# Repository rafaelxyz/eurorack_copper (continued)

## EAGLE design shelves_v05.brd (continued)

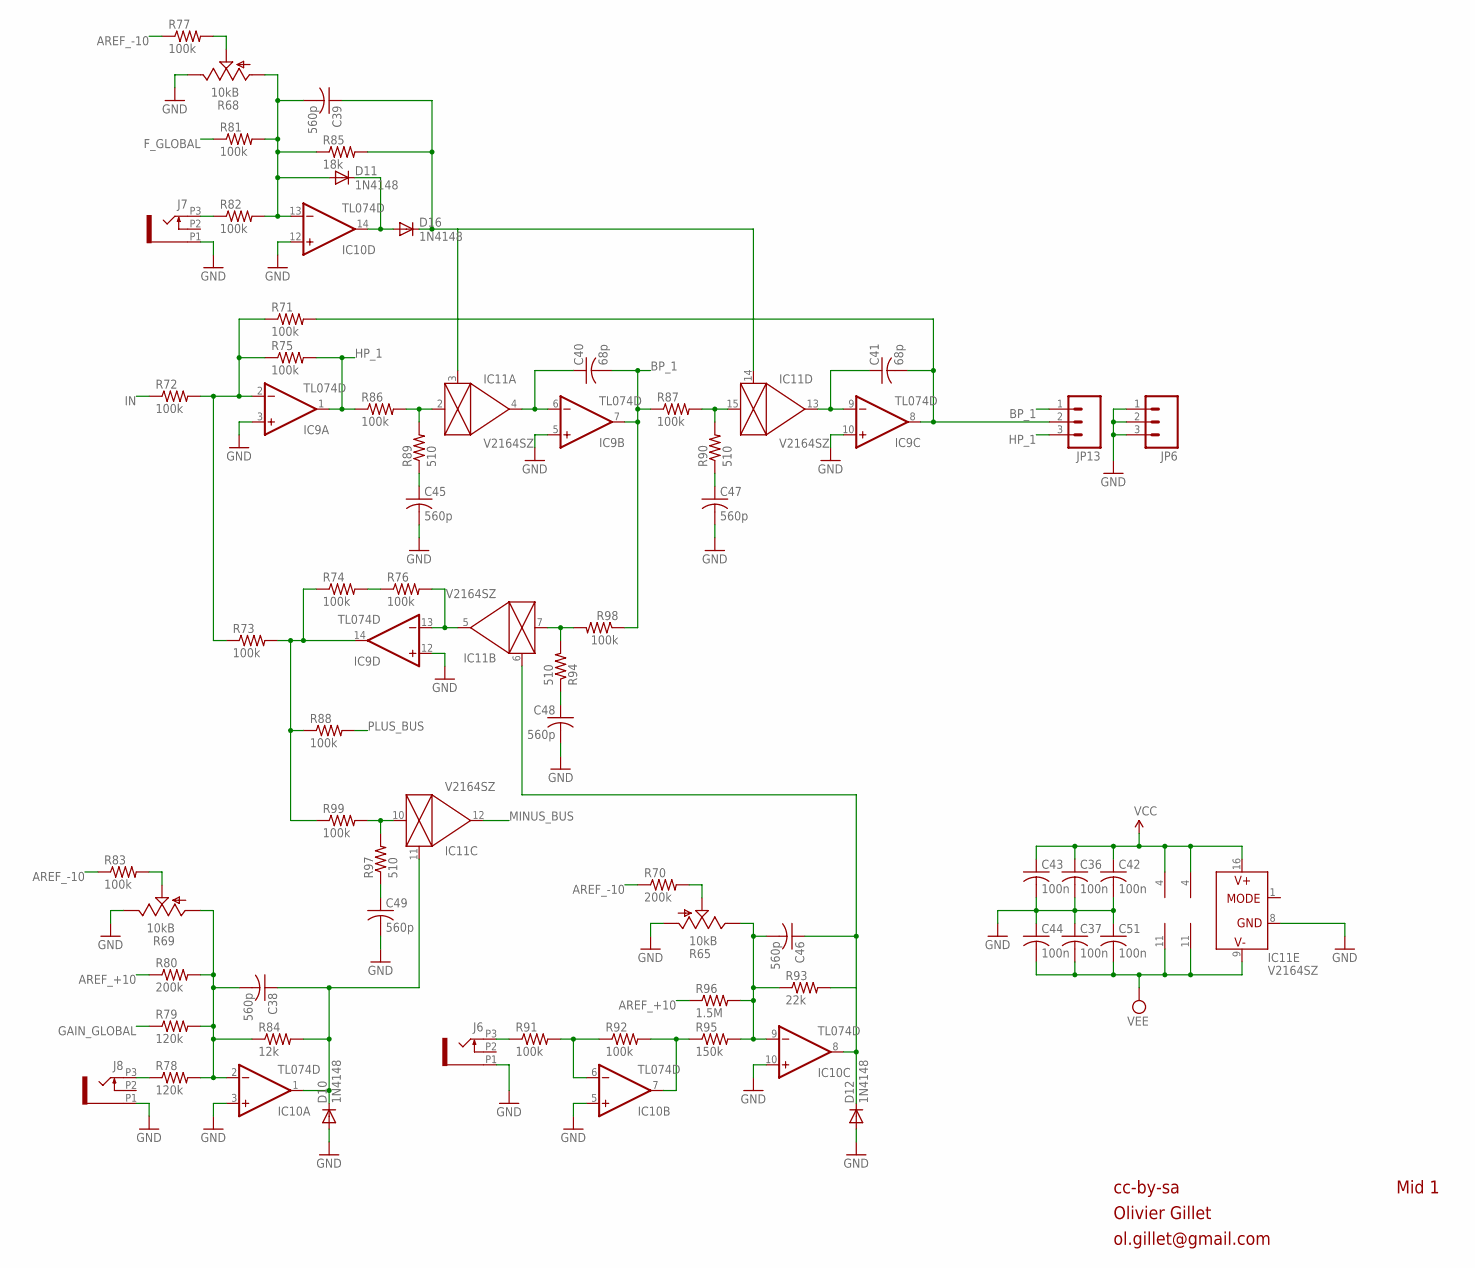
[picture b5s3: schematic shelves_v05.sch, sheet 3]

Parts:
C36, C37, C42, C43, C44, C51: 100n; C0603
C38, C39, C45, C46, C47, C48, C49: 560p; C0603
C40, C41: 68p; C0603
D10, D11, D12, D16: 1N4148; SOD323-W
IC9, IC10: TL074D; SO14
IC11: V2164SZ; SOIC16N
J6, J7, J8: PJ301_THONKICONN6; WQP_PJ_301M6
JP6, JP13: M03PTH; 1X03
R65: 10kB; ALPS_POT_VERTICAL
R68, R69: 10kB; ALPS_POT_VERTICAL_PS
R70, R80: 200k; R0603
R71, R72, R73, R74, R75, R76, R77, R81, R82, R83, R86, R87, R88, R91, R92, R98, R99: 100k; R0603
R78, R79: 120k; R0603
R84: 12k; R0603
R85: 18k; R0603
R89, R90, R94, R97: 510; R0603
R93: 22k; R0603
R95: 150k; R0603
R96: 1.5M; R0603

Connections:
AREF_+10: R80.1, R96.1; also elsewhere on the board
AREF_-10: R70.1, R77.1, R83.1; also elsewhere on the board
BP_1: C40.2, IC9.7 (OUT), JP13.1, R87.1, R98.1
F_GLOBAL: R81.1; also elsewhere on the board
GAIN_GLOBAL: R79.1; also elsewhere on the board
GND: C36.2, C37.1, C42.2, C43.2, C44.1, C45.2, C47.2, C48.2, C49.2, C51.1, D10.A, D12.A, IC9.3 (+IN), IC9.5 (+IN), IC9.10 (+IN), IC9.12 (+IN), IC10.3 (+IN), IC10.5 (+IN), IC10.10 (+IN), IC10.12 (+IN), IC11.8 (GND), J6.P1 (1), J7.P1 (1), J8.P1 (1), JP6.1, JP6.2, JP6.3, R65.P$3 (A), R68.P$1 (E), R69.P$1 (E); also elsewhere on the board
HP_1: IC9.1 (OUT), JP13.3, R75.2, R86.1
IN: R72.1; also elsewhere on the board
MID1_F2: C39.1, D16.C, IC11.3 (CTRL), IC11.14 (CTRL), R85.2
MINUS_BUS: IC11.12 (OUT); also elsewhere on the board
unnamed: D11.C, D16.A, IC10.14 (OUT)
unnamed: IC10.7 (OUT), R92.2, R95.1
unnamed: C45.1, R89.1
unnamed: J7.P3 (3), R82.1
unnamed: R68.P$2 (S), R77.2
unnamed: C38.1, D10.C, IC10.1 (OUT), IC11.11 (CTRL), R84.2
unnamed: C38.2, IC10.2 (-IN), R69.P$3 (A), R78.2, R79.2, R80.2, R84.1
unnamed: J8.P3 (3), R78.1
unnamed: R69.P$2 (S), R83.2
unnamed: C39.2, D11.A, IC10.13 (-IN), R68.P$3 (A), R81.2, R82.2, R85.1
unnamed: C49.1, R97.1
unnamed: IC11.10 (IN), R97.2, R99.2
unnamed: IC9.2 (-IN), R71.1, R72.2, R73.1, R75.1
unnamed: IC11.2 (IN), R86.2, R89.2
unnamed: C40.1, IC9.6 (-IN), IC11.4 (OUT)
unnamed: C47.1, R90.1
unnamed: IC11.15 (IN), R87.2, R90.2
unnamed: C41.1, IC9.9 (-IN), IC11.13 (OUT)
unnamed: C41.2, IC9.8 (OUT), JP13.2, R71.2
unnamed: C48.1, R94.1
unnamed: IC11.7 (IN), R94.2, R98.2
unnamed: IC9.13 (-IN), IC11.5 (OUT), R76.2
unnamed: R74.2, R76.1
unnamed: IC9.14 (OUT), R73.2, R74.1, R88.1, R99.1
unnamed: C46.1, D12.C, IC10.8 (OUT), IC11.6 (CTRL), R93.2
unnamed: C46.2, IC10.9 (-IN), R65.P$1 (E), R93.1, R95.2, R96.2
unnamed: R65.P$2 (S), R70.2
unnamed: J6.P3 (3), R91.1
unnamed: IC10.6 (-IN), R91.2, R92.1
PLUS_BUS: R88.2; also elsewhere on the board
VCC: C36.1, C42.1, C43.1, IC9.4 (V+), IC10.4 (V+), IC11.16 (V+); also elsewhere on the board
VEE: C37.2, C44.2, C51.2, IC9.11 (V-), IC10.11 (V-), IC11.9 (V-); also elsewhere on the board

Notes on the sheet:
cc-by-sa
Olivier Gillet
ol.gillet@gmail.com
Mid 1

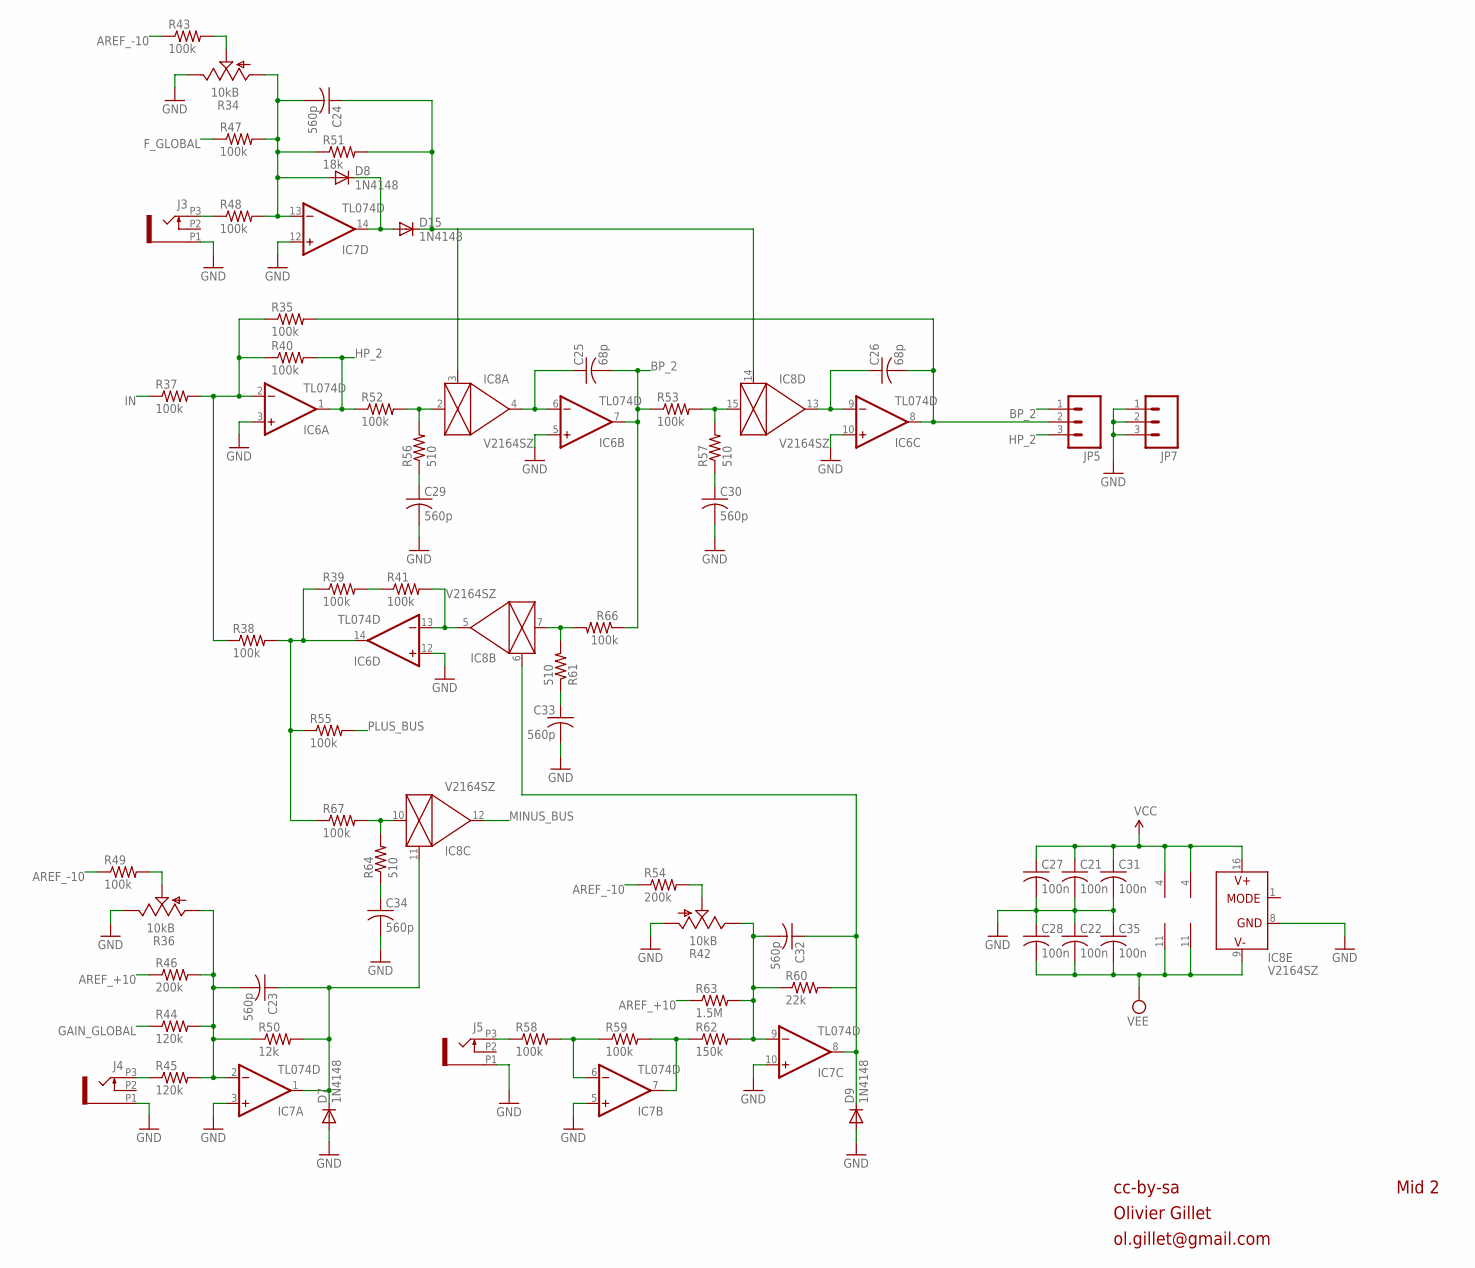
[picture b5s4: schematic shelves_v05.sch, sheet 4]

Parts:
C21, C22, C27, C28, C31, C35: 100n; C0603
C23, C24, C29, C30, C32, C33, C34: 560p; C0603
C25, C26: 68p; C0603
D7, D8, D9, D15: 1N4148; SOD323-W
IC6, IC7: TL074D; SO14
IC8: V2164SZ; SOIC16N
J3, J4, J5: PJ301_THONKICONN6; WQP_PJ_301M6
JP5, JP7: M03PTH; 1X03
R34, R36: 10kB; ALPS_POT_VERTICAL_PS
R35, R37, R38, R39, R40, R41, R43, R47, R48, R49, R52, R53, R55, R58, R59, R66, R67: 100k; R0603
R42: 10kB; ALPS_POT_VERTICAL
R44, R45: 120k; R0603
R46, R54: 200k; R0603
R50: 12k; R0603
R51: 18k; R0603
R56, R57, R61, R64: 510; R0603
R60: 22k; R0603
R62: 150k; R0603
R63: 1.5M; R0603

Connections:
AREF_+10: R46.1, R63.1; also elsewhere on the board
AREF_-10: R43.1, R49.1, R54.1; also elsewhere on the board
BP_2: C25.2, IC6.7 (OUT), JP5.1, R53.1, R66.1
F_GLOBAL: R47.1; also elsewhere on the board
GAIN_GLOBAL: R44.1; also elsewhere on the board
GND: C21.2, C22.1, C27.2, C28.1, C29.2, C30.2, C31.2, C33.2, C34.2, C35.1, D7.A, D9.A, IC6.3 (+IN), IC6.5 (+IN), IC6.10 (+IN), IC6.12 (+IN), IC7.3 (+IN), IC7.5 (+IN), IC7.10 (+IN), IC7.12 (+IN), IC8.8 (GND), J3.P1 (1), J4.P1 (1), J5.P1 (1), JP7.1, JP7.2, JP7.3, R34.P$1 (E), R36.P$1 (E), R42.P$3 (A); also elsewhere on the board
HP_2: IC6.1 (OUT), JP5.3, R40.2, R52.1
IN: R37.1; also elsewhere on the board
MID1_F1: C24.1, D15.C, IC8.3 (CTRL), IC8.14 (CTRL), R51.2
MINUS_BUS: IC8.12 (OUT); also elsewhere on the board
unnamed: D8.C, D15.A, IC7.14 (OUT)
unnamed: C29.1, R56.1
unnamed: IC7.7 (OUT), R59.2, R62.1
unnamed: J3.P3 (3), R48.1
unnamed: R34.P$2 (S), R43.2
unnamed: C23.1, D7.C, IC7.1 (OUT), IC8.11 (CTRL), R50.2
unnamed: C23.2, IC7.2 (-IN), R36.P$3 (A), R44.2, R45.2, R46.2, R50.1
unnamed: J4.P3 (3), R45.1
unnamed: R36.P$2 (S), R49.2
unnamed: C24.2, D8.A, IC7.13 (-IN), R34.P$3 (A), R47.2, R48.2, R51.1
unnamed: C34.1, R64.1
unnamed: IC8.10 (IN), R64.2, R67.2
unnamed: IC6.2 (-IN), R35.1, R37.2, R38.1, R40.1
unnamed: IC8.2 (IN), R52.2, R56.2
unnamed: C25.1, IC6.6 (-IN), IC8.4 (OUT)
unnamed: C30.1, R57.1
unnamed: IC8.15 (IN), R53.2, R57.2
unnamed: C26.1, IC6.9 (-IN), IC8.13 (OUT)
unnamed: C26.2, IC6.8 (OUT), JP5.2, R35.2
unnamed: C33.1, R61.1
unnamed: IC8.7 (IN), R61.2, R66.2
unnamed: IC6.13 (-IN), IC8.5 (OUT), R41.2
unnamed: R39.2, R41.1
unnamed: IC6.14 (OUT), R38.2, R39.1, R55.1, R67.1
unnamed: C32.1, D9.C, IC7.8 (OUT), IC8.6 (CTRL), R60.2
unnamed: C32.2, IC7.9 (-IN), R42.P$1 (E), R60.1, R62.2, R63.2
unnamed: IC7.6 (-IN), R58.2, R59.1
unnamed: R42.P$2 (S), R54.2
unnamed: J5.P3 (3), R58.1
PLUS_BUS: R55.2; also elsewhere on the board
VCC: C21.1, C27.1, C31.1, IC6.4 (V+), IC7.4 (V+), IC8.16 (V+); also elsewhere on the board
VEE: C22.2, C28.2, C35.2, IC6.11 (V-), IC7.11 (V-), IC8.9 (V-); also elsewhere on the board

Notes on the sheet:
cc-by-sa
Olivier Gillet
ol.gillet@gmail.com
Mid 2

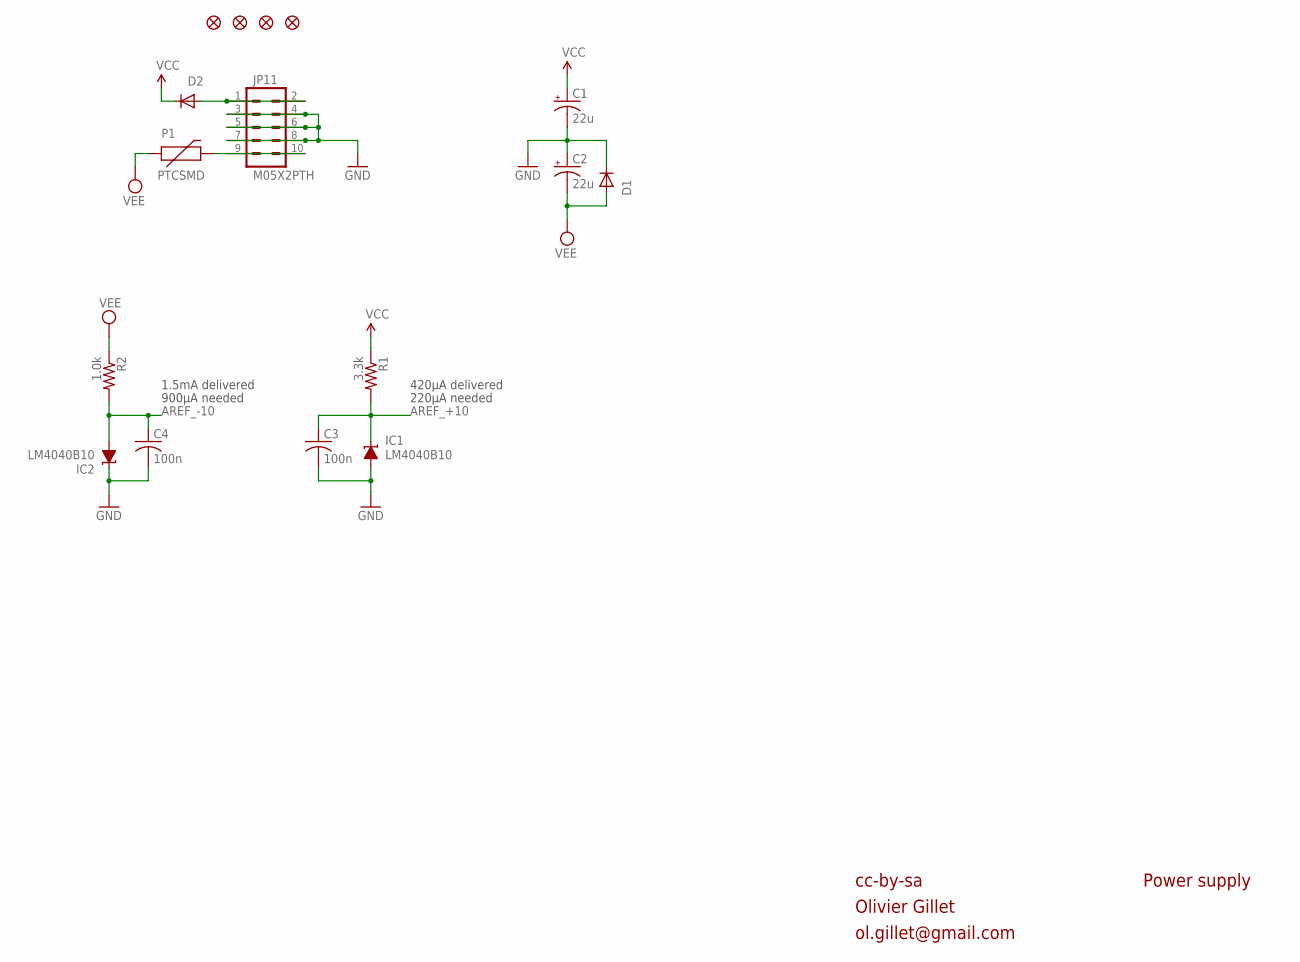
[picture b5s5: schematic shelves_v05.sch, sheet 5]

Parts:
C1, C2: 22u; PANASONIC_C
C3, C4: 100n; C0603
D1, D2: 1N5819HW; SOD123
IC1, IC2: LM4040B10; DBZ_R-PDSO-G3
JP1, JP2, JP3, JP4: FIDUCIAL1X2; FIDUCIAL-1X2
JP11: M05X2PTH; AVR_ICSP
P1: PTCSMD; PTC-1206
R1: 3.3k; R0603
R2: 1.0k; R0603

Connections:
AREF_+10: C3.1, IC1.1 (C), R1.2; also elsewhere on the board
AREF_-10: C4.1, IC2.2 (A), R2.2; also elsewhere on the board
GND: C1.-, C2.+, C3.2, C4.2, D1.C, IC1.2 (A), IC2.1 (C), JP11.3, JP11.4, JP11.5, JP11.6, JP11.7, JP11.8; also elsewhere on the board
unnamed: D2.A, JP11.1, JP11.2
unnamed: JP11.9, JP11.10, P1.2
VCC: C1.+, D2.C, R1.1; also elsewhere on the board
VEE: C2.-, D1.A, P1.1, R2.1; also elsewhere on the board

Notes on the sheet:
cc-by-sa
Olivier Gillet
ol.gillet@gmail.com
Power supply
900µA needed
220µA needed
1.5mA delivered
420µA delivered

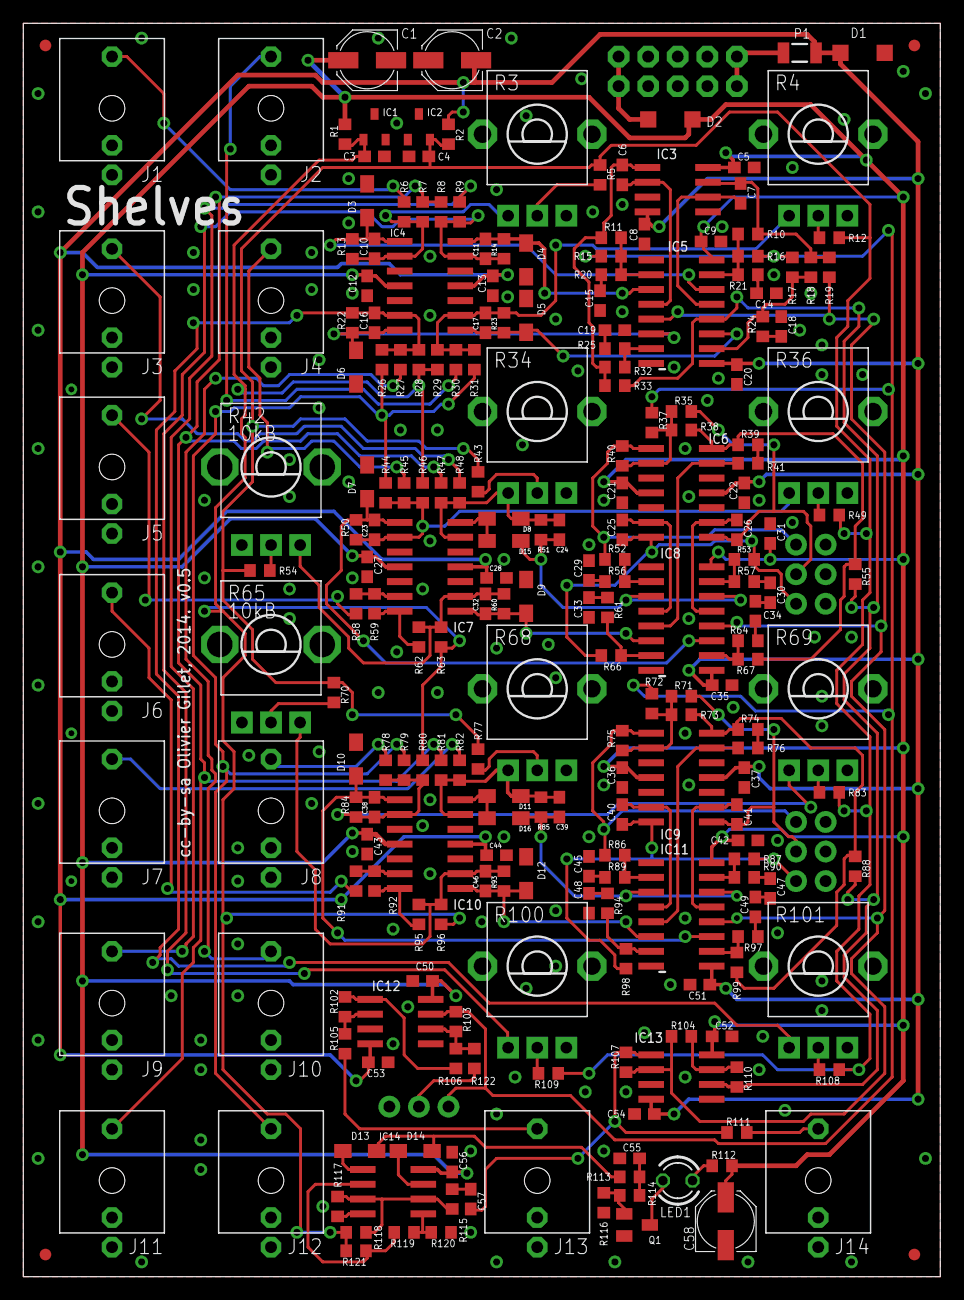
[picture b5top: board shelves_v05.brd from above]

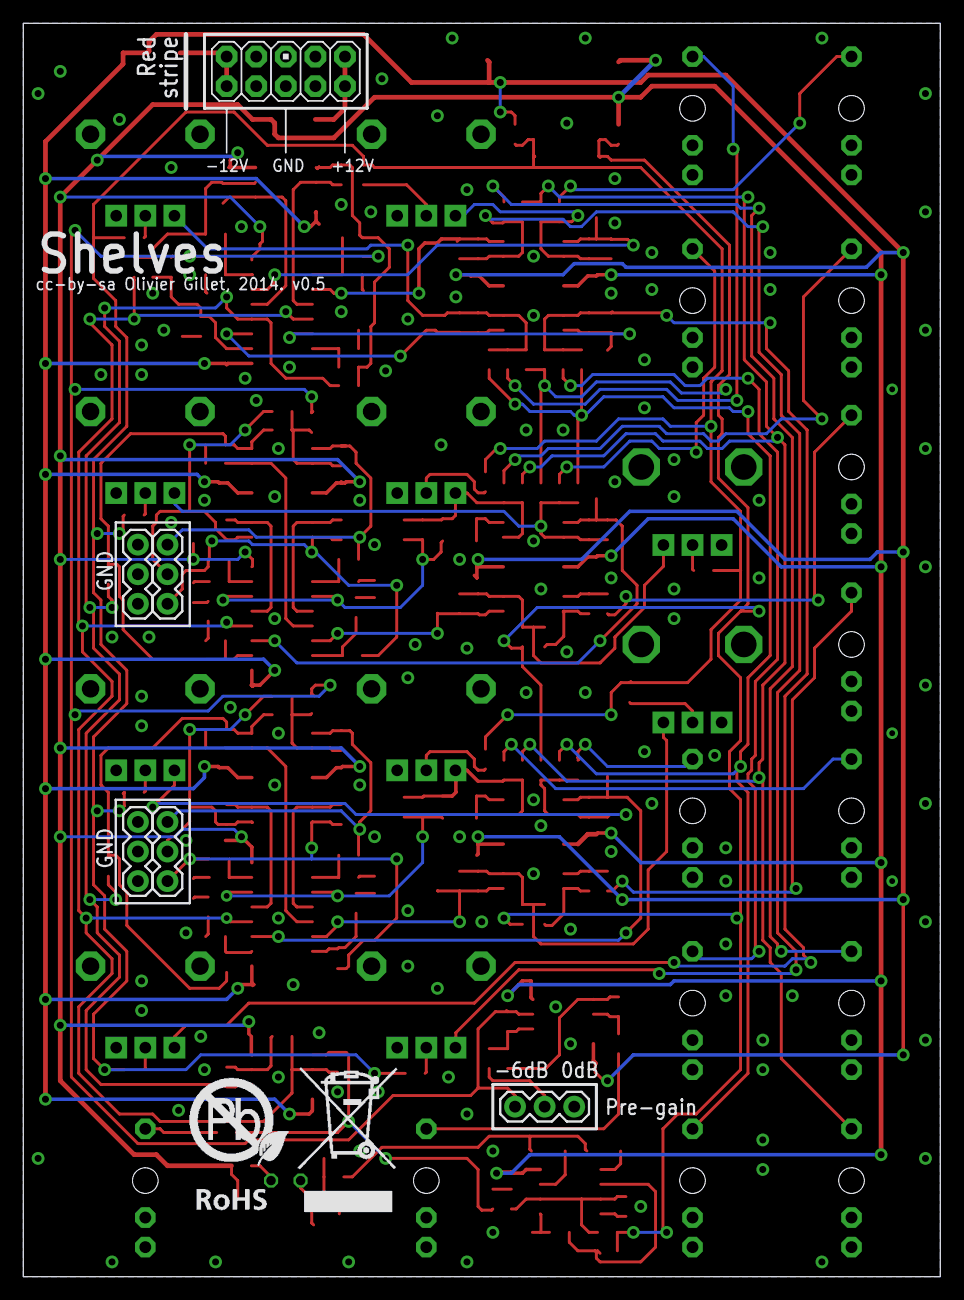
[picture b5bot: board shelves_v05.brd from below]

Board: 2 copper layers, 78.7 x 107.6 mm, 238 parts (7 on the bottom side), 123 nets.

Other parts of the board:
U$2: ROHS_BIG

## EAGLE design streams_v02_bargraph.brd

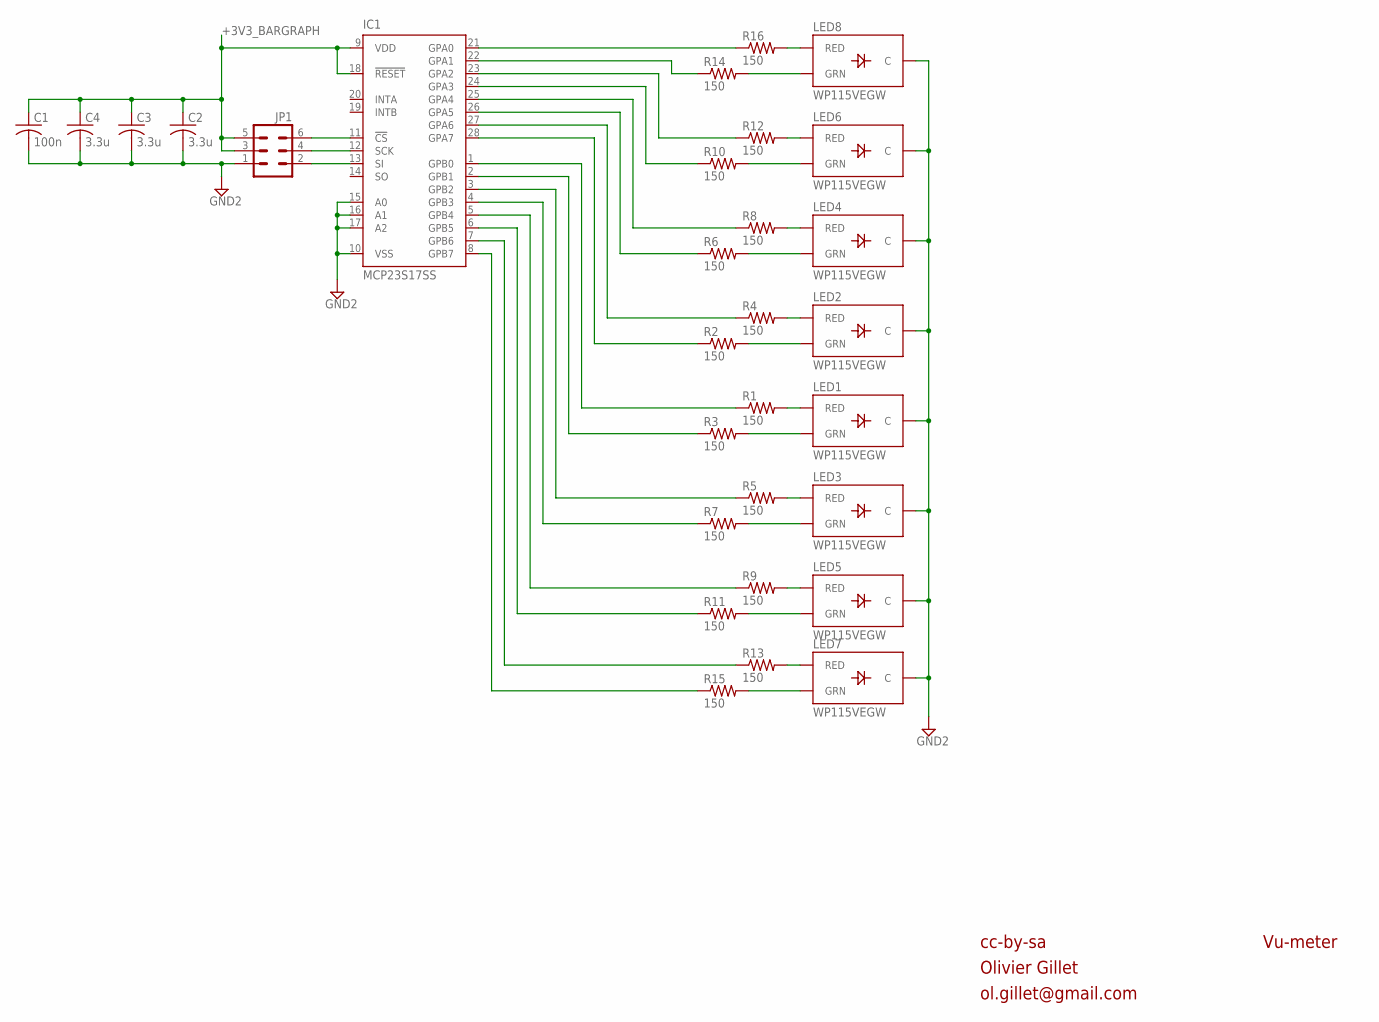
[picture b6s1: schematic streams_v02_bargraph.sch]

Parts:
C1: 100n; C0603
C2, C3, C4: 3.3u; C0603
IC1: MCP23S17SS; SSOP28
JP1: M03X2; 2X3
LED1, LED2, LED3, LED4, LED5, LED6, LED7, LED8: WP115VEGW; LED-BICOLOR-THROUGHHOLE
R1, R2, R3, R4, R5, R6, R7, R8, R9, R10, R11, R12, R13, R14, R15, R16: 150; R0603

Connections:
+3V3_BARGRAPH: C1.1, C2.1, C3.1, C4.1, IC1.9 (VDD), IC1.18 (!RESET), JP1.3, JP1.5
GND2: C1.2, C2.2, C3.2, C4.2, IC1.10 (VSS), IC1.15 (A0), IC1.16 (A1), IC1.17 (A2), JP1.1, LED1.2 (C), LED2.2 (C), LED3.2 (C), LED4.2 (C), LED5.2 (C), LED6.2 (C), LED7.2 (C), LED8.2 (C)
unnamed: IC1.11 (!CS), JP1.6
unnamed: IC1.12 (SCK), JP1.4
unnamed: LED1.3 (RED), R1.2
unnamed: IC1.13 (SI), JP1.2
unnamed: LED1.1 (GRN), R3.2
unnamed: LED3.3 (RED), R5.2
unnamed: LED3.1 (GRN), R7.2
unnamed: LED5.3 (RED), R9.2
unnamed: LED5.1 (GRN), R11.2
unnamed: LED7.3 (RED), R13.2
unnamed: LED7.1 (GRN), R15.2
unnamed: LED8.3 (RED), R16.2
unnamed: LED8.1 (GRN), R14.2
unnamed: LED6.3 (RED), R12.2
unnamed: LED6.1 (GRN), R10.2
unnamed: LED4.3 (RED), R8.2
unnamed: LED4.1 (GRN), R6.2
unnamed: LED2.3 (RED), R4.2
unnamed: LED2.1 (GRN), R2.2
unnamed: IC1.27 (GPA6), R4.1
unnamed: IC1.28 (GPA7), R2.1
unnamed: IC1.1 (GPB0), R1.1
unnamed: IC1.2 (GPB1), R3.1
unnamed: IC1.21 (GPA0), R16.1
unnamed: IC1.22 (GPA1), R14.1
unnamed: IC1.23 (GPA2), R12.1
unnamed: IC1.24 (GPA3), R10.1
unnamed: IC1.25 (GPA4), R8.1
unnamed: IC1.26 (GPA5), R6.1
unnamed: IC1.3 (GPB2), R5.1
unnamed: IC1.4 (GPB3), R7.1
unnamed: IC1.5 (GPB4), R9.1
unnamed: IC1.6 (GPB5), R11.1
unnamed: IC1.7 (GPB6), R13.1
unnamed: IC1.8 (GPB7), R15.1

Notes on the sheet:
cc-by-sa
Olivier Gillet
ol.gillet@gmail.com
Vu-meter

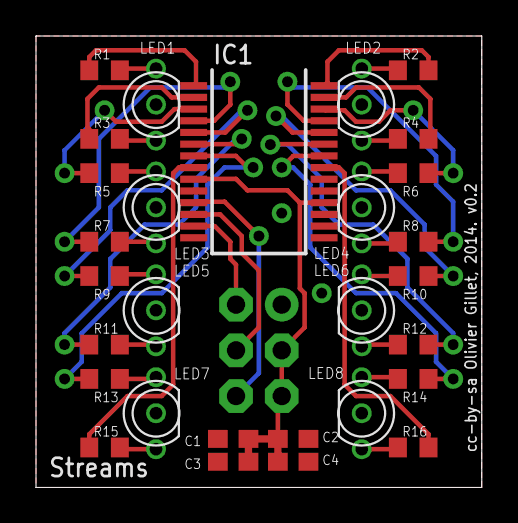
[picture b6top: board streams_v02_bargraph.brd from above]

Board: 2 copper layers, 24.8 x 25.1 mm, 30 parts (1 on the bottom side), 37 nets.

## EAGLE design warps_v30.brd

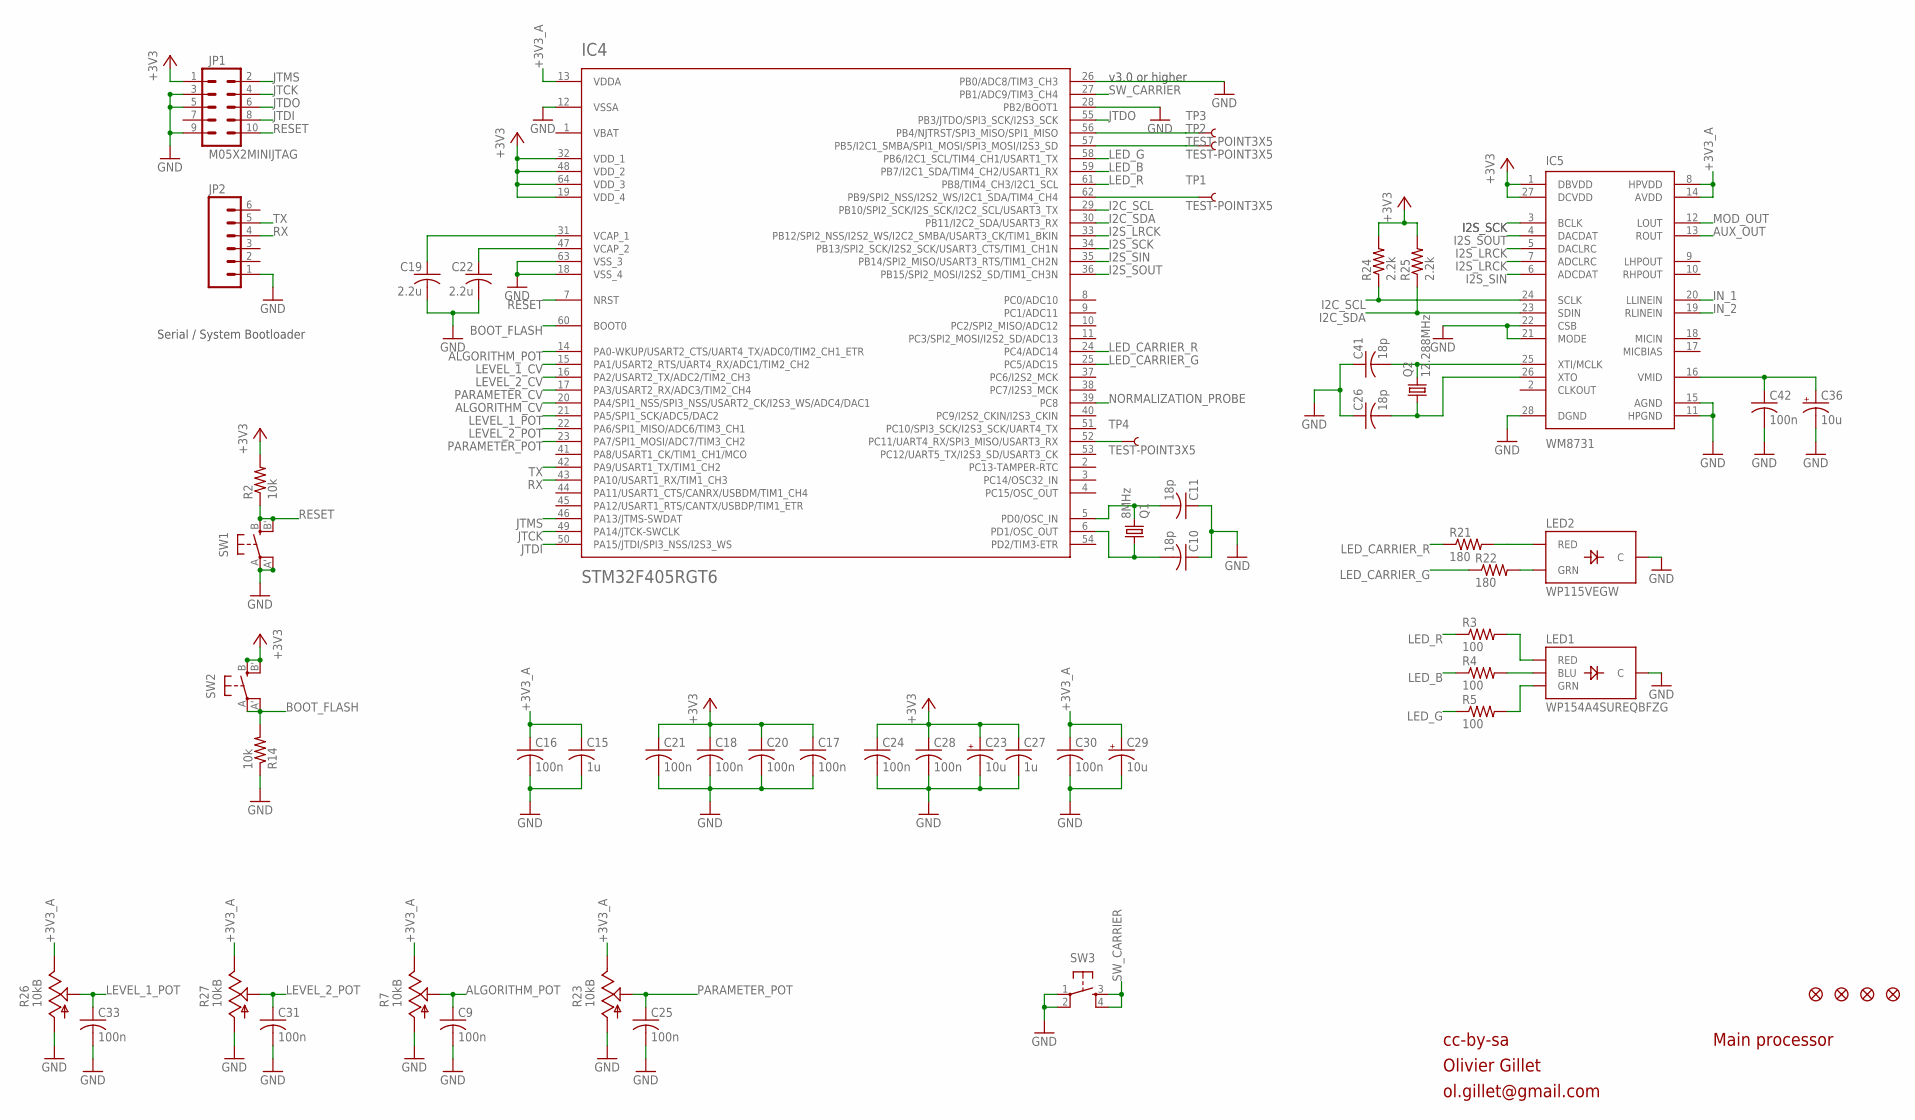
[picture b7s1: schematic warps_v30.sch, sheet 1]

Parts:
C9, C16, C17, C18, C20, C21, C24, C25, C28, C30, C31, C33, C42: 100n; C0603
C10, C11, C26, C41: 18p; C0603
C15, C27: 1u; C0603
C19, C22: 2.2u; C0805
C23, C29, C36: 10u; PANASONIC_A
F1, F2, F3, F4: FIDUCIAL1X2; FIDUCIAL-1X2
IC4: STM32F405RGT6; TQFP-10X10-64
IC5: WM8731; SSOP28
JP1: M05X2MINIJTAG; 2X5-1.27
JP2: M06SIP; 1X06
LED1: WP154A4SUREQBFZG; LED-TRICOLOR-THROUGHHOLE
LED2: WP115VEGW; LED-BICOLOR-THROUGHHOLE
Q1: 8MHz; HC49UP
Q2: 12.288MHz; HC49UP
R2, R14: 10k; R0603
R3, R4, R5: 100; R0603
R7, R23: 10kB; ALPS_POT_VERTICAL_PS
R21, R22: 180; R0603
R24, R25: 2.2k; R0603
R26, R27: 10kB; ALPS_POT_VERTICAL
SW1, SW2: EVQQ2; EVQ-Q2
SW3: TAC_SWITCHPTH; TACTILE-PTH
TP1, TP2, TP3, TP4: TEST-POINT3X5; PAD.03X.05

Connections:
+3V3: C17.1, C18.1, C20.1, C21.1, C23.+, C24.1, C27.1, C28.1, IC4.19 (VDD_4), IC4.32 (VDD_1), IC4.48 (VDD_2), IC4.64 (VDD_3), IC5.1 (DBVDD), IC5.27 (DCVDD), JP1.1, R2.2, R24.2, R25.2, SW2.B (S), SW2.B' (S1); also elsewhere on the board
+3V3_A: C15.1, C16.1, C29.+, C30.1, IC4.13 (VDDA), IC5.8 (HPVDD), IC5.14 (AVDD), R7.P$1 (E), R23.P$1 (E), R26.P$1 (E), R27.P$1 (E); also elsewhere on the board
ALGORITHM_CV: IC4.20 (PA4/SPI1_NSS/SPI3_NSS/USART2_CK/I2S3_WS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); also elsewhere on the board
ALGORITHM_POT: C9.1, IC4.14 (PA0-WKUP/USART2_CTS/UART4_TX/ADC0/TIM2_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), R7.P$2 (S)
AUX_OUT: IC5.13 (ROUT); also elsewhere on the board
BOOT_FLASH: IC4.60 (BOOT0), R14.2, SW2.A, SW2.A' (P1)
GND: C9.2, C10.1, C11.1, C15.2, C16.2, C17.2, C18.2, C19.2, C20.2, C21.2, C22.2, C23.-, C24.2, C25.2, C26.1, C27.2, C28.2, C29.-, C30.2, C31.2, C33.2, C36.-, C41.1, C42.2, IC4.12 (VSSA), IC4.18 (VSS_4), IC4.26 (PB0/ADC8/TIM3_CH3), IC4.28 (PB2/BOOT1), IC4.63 (VSS_3), IC5.11 (HPGND), IC5.15 (AGND), IC5.21 (MODE), IC5.22 (CSB), IC5.28 (DGND), JP1.3, JP1.5, JP1.9, JP2.1, LED1.GND (C), LED2.2 (C), R7.P$3 (A), R14.1, R23.P$3 (A), R26.P$3 (A), R27.P$3 (A), SW1.A, SW1.A' (P1), SW3.1, SW3.2; also elsewhere on the board
I2C_SCL: IC4.29 (PB10/SPI2_SCK/I2S_SCK/I2C2_SCL/USART3_TX), IC5.24 (SCLK), R24.1
I2C_SDA: IC4.30 (PB11/I2C2_SDA/USART3_RX), IC5.23 (SDIN), R25.1
I2S_LRCK: IC4.33 (PB12/SPI2_NSS/I2S2_WS/I2C2_SMBA/USART3_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), IC5.5 (DACLRC), IC5.7 (ADCLRC)
I2S_SCK: IC4.34 (PB13/SPI2_SCK/I2S2_SCK/USART3_CTS/TIM1_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), IC5.3 (BCLK)
I2S_SIN: IC4.35 (PB14/SPI2_MISO/USART3_RTS/TIM1_CH2N), IC5.6 (ADCDAT)
I2S_SOUT: IC4.36 (PB15/SPI2_MOSI/I2S2_SD/TIM1_CH3N), IC5.4 (DACDAT)
IN_1: IC5.20 (LLINEIN); also elsewhere on the board
IN_2: IC5.19 (RLINEIN); also elsewhere on the board
JTCK: IC4.49 (PA14/JTCK-SWCLK), JP1.4
JTDI: IC4.50 (PA15/JTDI/SPI3_NSS/I2S3_WS), JP1.8
JTDO: IC4.55 (PB3/JTDO/SPI3_SCK/I2S3_SCK), JP1.6
JTMS: IC4.46 (PA13/JTMS-SWDAT), JP1.2
LED_B: IC4.59 (PB7/I2C1_SDA/TIM4_CH2/USART1_RX), R4.1
LED_CARRIER_G: IC4.25 (PC5/ADC15), R22.1
LED_CARRIER_R: IC4.24 (PC4/ADC14), R21.1
LED_G: IC4.58 (PB6/I2C1_SCL/TIM4_CH1/USART1_TX), R5.1
LED_R: IC4.61 (PB8/TIM4_CH3/I2C1_SCL), R3.1
LEVEL_1_CV: IC4.15 (PA1/USART2_RTS/UART4_RX/ADC1/TIM2_CH2); also elsewhere on the board
LEVEL_1_POT: C33.1, IC4.21 (PA5/SPI1_SCK/ADC5/DAC2), R26.P$2 (S)
LEVEL_2_CV: IC4.16 (PA2/USART2_TX/ADC2/TIM2_CH3); also elsewhere on the board
LEVEL_2_POT: C31.1, IC4.22 (PA6/SPI1_MISO/ADC6/TIM3_CH1), R27.P$2 (S)
MOD_OUT: IC5.12 (LOUT); also elsewhere on the board
unnamed: LED2.3 (RED), R21.2
unnamed: C11.2, IC4.5 (PD0/OSC_IN), Q1.2
unnamed: C10.2, IC4.6 (PD1/OSC_OUT), Q1.1
unnamed: C22.1, IC4.47 (VCAP_2)
unnamed: LED2.1 (GRN), R22.2
unnamed: C36.+, C42.1, IC5.16 (VMID)
unnamed: C19.1, IC4.31 (VCAP_1)
unnamed: IC4.56 (PB4/NJTRST/SPI3_MISO/SPI1_MISO), TP3.P$1
unnamed: IC4.57 (PB5/I2C1_SMBA/SPI1_MOSI/SPI3_MOSI/I2S3_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), TP2.P$1
unnamed: IC4.52 (PC11/UART4_RX/SPI3_MISO/USART3_RX), TP4.P$1
unnamed: IC4.62 (PB9/SPI2_NSS/I2S2_WS/I2C1_SDA/TIM4_CH4), TP1.P$1
unnamed: LED1.RED, R3.2
unnamed: LED1.BLU, R4.2
unnamed: LED1.GRN, R5.2
unnamed: C41.2, IC5.25 (XTI/MCLK), Q2.2
unnamed: C26.2, IC5.26 (XTO), Q2.1
NORMALIZATION_PROBE: IC4.39 (PC8); also elsewhere on the board
PARAMETER_CV: IC4.17 (PA3/USART2_RX/ADC3/TIM2_CH4); also elsewhere on the board
PARAMETER_POT: C25.1, IC4.23 (PA7/SPI1_MOSI/ADC7/TIM3_CH2), R23.P$2 (S)
RESET: IC4.7 (NRST), JP1.10, R2.1, SW1.B (S), SW1.B' (S1)
RX: IC4.43 (PA10/USART1_RX/TIM1_CH3), JP2.4
SW_CARRIER: IC4.27 (PB1/ADC9/TIM3_CH4), SW3.3, SW3.4
TX: IC4.42 (PA9/USART1_TX/TIM1_CH2), JP2.5
VBAT: IC4.1 (VBAT)

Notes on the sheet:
cc-by-sa
Olivier Gillet
ol.gillet@gmail.com
Main processor
Serial / System Bootloader
v3.0 or higher

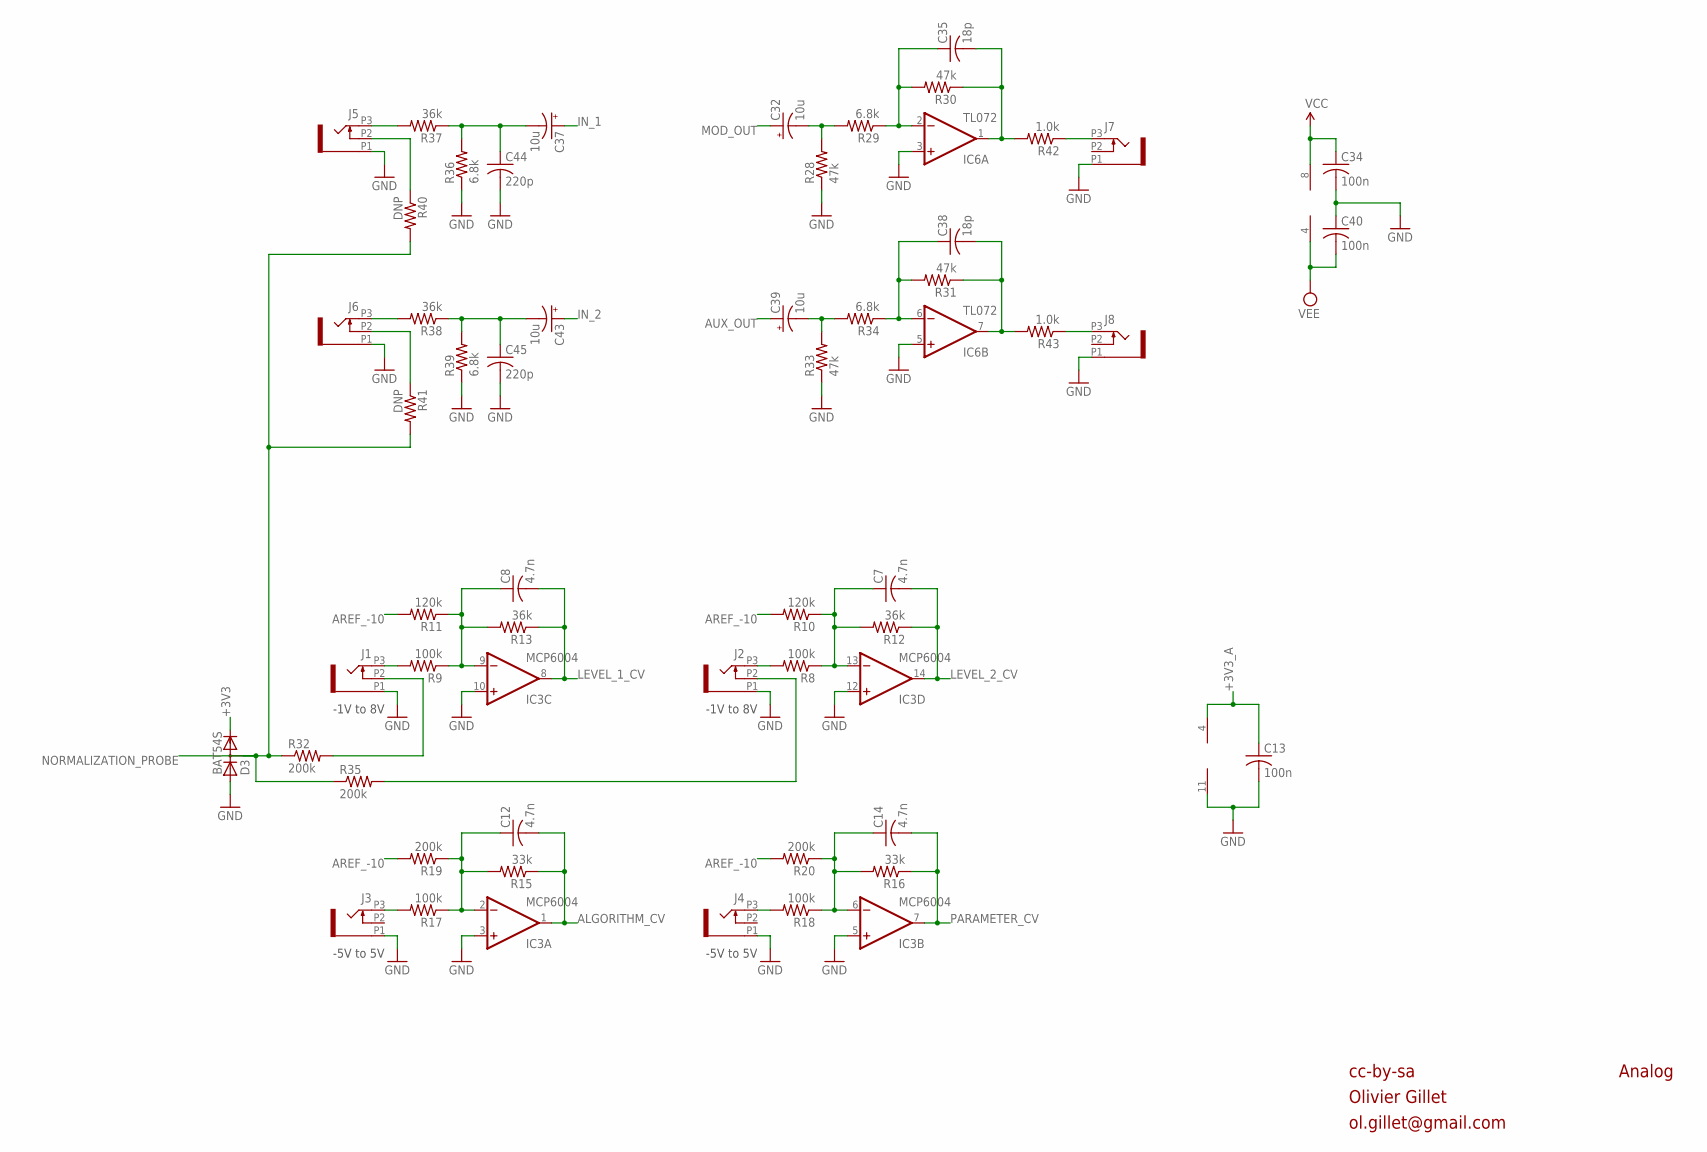
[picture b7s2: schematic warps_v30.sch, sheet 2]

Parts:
C7, C8, C12, C14: 4.7n; C0603
C13, C34, C40: 100n; C0603
C32, C37, C39, C43: 10u; PANASONIC_A
C35, C38: 18p; C0603
C44, C45: 220p; C0603
D3: BAT54S; SOT23
IC3: MCP6004; SO14
IC6: TL072; SO08
J1, J2, J3, J4, J5, J6, J7, J8: PJ301_THONKICONN6; WQP_PJ_301M6
R8, R9, R17, R18: 100k; R0603
R10, R11: 120k; R0603
R12, R13, R37, R38: 36k; R0603
R15, R16: 33k; R0603
R19, R20, R32, R35: 200k; R0603
R28, R30, R31, R33: 47k; R0603
R29, R34, R36, R39: 6.8k; R0603
R40, R41: DNP; R0603
R42, R43: 1.0k; R0603

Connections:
+3V3: D3.2 (C); also elsewhere on the board
+3V3_A: C13.1, IC3.4 (V+); also elsewhere on the board
ALGORITHM_CV: C12.2, IC3.1 (OUT), R15.1; also elsewhere on the board
AREF_-10: R10.2, R11.2, R19.2, R20.2; also elsewhere on the board
AUX_OUT: C39.+; also elsewhere on the board
GND: C13.2, C34.2, C40.1, C44.2, C45.2, D3.1 (A), IC3.3 (+IN), IC3.5 (+IN), IC3.10 (+IN), IC3.11 (V-), IC3.12 (+IN), IC6.3 (+IN), IC6.5 (+IN), J1.P1 (1), J2.P1 (1), J3.P1 (1), J4.P1 (1), J5.P1 (1), J6.P1 (1), J7.P1 (1), J8.P1 (1), R28.1, R33.1, R36.1, R39.1; also elsewhere on the board
IN_1: C37.+; also elsewhere on the board
IN_2: C43.+; also elsewhere on the board
LEVEL_1_CV: C8.2, IC3.8 (OUT), R13.1; also elsewhere on the board
LEVEL_2_CV: C7.2, IC3.14 (OUT), R12.1; also elsewhere on the board
MOD_OUT: C32.+; also elsewhere on the board
unnamed: J1.P3 (3), R9.2
unnamed: C8.1, IC3.9 (-IN), R9.1, R11.1, R13.2
unnamed: J2.P3 (3), R8.2
unnamed: C7.1, IC3.13 (-IN), R8.1, R10.1, R12.2
unnamed: J4.P3 (3), R18.2
unnamed: J1.P2 (2), R32.2
unnamed: J3.P3 (3), R17.2
unnamed: C12.1, IC3.2 (-IN), R15.2, R17.1, R19.1
unnamed: J2.P2 (2), R35.2
unnamed: C14.1, IC3.6 (-IN), R16.2, R18.1, R20.1
unnamed: C37.-, C44.1, R36.2, R37.1
unnamed: J6.P3 (3), R38.2
unnamed: J5.P3 (3), R37.2
unnamed: C43.-, C45.1, R38.1, R39.2
unnamed: C39.-, R33.2, R34.2
unnamed: C38.1, IC6.6 (-IN), R31.2, R34.1
unnamed: C38.2, IC6.7 (OUT), R31.1, R43.2
unnamed: J8.P3 (3), R43.1
unnamed: C32.-, R28.2, R29.2
unnamed: C35.1, IC6.2 (-IN), R29.1, R30.2
unnamed: C35.2, IC6.1 (OUT), R30.1, R42.2
unnamed: J7.P3 (3), R42.1
unnamed: J6.P2 (2), R41.1
unnamed: J5.P2 (2), R40.1
NORMALIZATION_PROBE: D3.3 (AC), R32.1, R35.1, R40.2, R41.2; also elsewhere on the board
PARAMETER_CV: C14.2, IC3.7 (OUT), R16.1; also elsewhere on the board
VCC: C34.1, IC6.8 (V+); also elsewhere on the board
VEE: C40.2, IC6.4 (V-); also elsewhere on the board

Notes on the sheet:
cc-by-sa
Olivier Gillet
ol.gillet@gmail.com
Analog
-1V to 8V
-5V to 5V
